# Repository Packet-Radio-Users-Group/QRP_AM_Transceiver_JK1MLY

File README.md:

ブロックダイアグラムが学べる　QRPトランシーバ基板

無線機の基本的な動作を知るため、振幅変調（amplitude modulation）を使った簡易的な無線機を作り、回路の定数やデバイスを変えたり、動作波形を見たりするする基板について扱う

以下の構成でファイルは保存する

assembly  提供する基板に部品を実装する手引き　pdf版の回路図、excel版の部品表を含む

caddata   KiCadのデータ

document  使っている部品、基板などに関する情報

guidance  どのように実験をしていくかの手引き

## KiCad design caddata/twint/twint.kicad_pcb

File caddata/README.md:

KICadデータ

am-pcb1
　思い立って最初に作ったもの
（この基板で実験して、28M・10mWの免許を取得）

am-pcb2
　pcb1を作り直そうとしたもの
（リファイン前提で先に番号を取ったが色々と変えることにしてボツ）

am-pcb3
　受信のミキサをICにしたもの
（動作を学ぶためにはトランジスタの考えに戻ってボツ）

am-pcb4
　実験用として使うための改良
（ハムフェア2024で頒布）

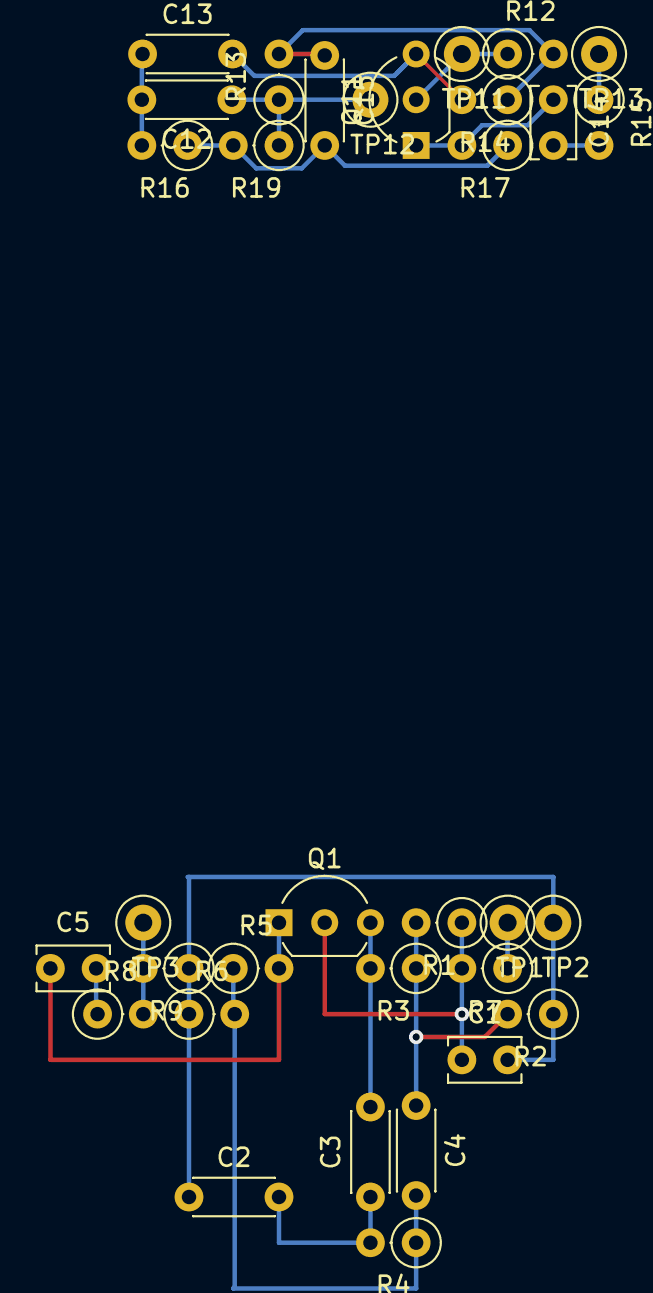
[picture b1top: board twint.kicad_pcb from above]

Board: 2 copper layers, 33 parts (0 on the bottom side), 18 nets.

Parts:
C1, C5, C14: 0.1u; C_Disc_P2.54mm
C2, C3, C12, C13: 0.01u; C_Disc_P5.12mm
C4, C15: 0.033u; C_Disc_P5.12mm
Q1, Q11: 2SC1815; TO-92_Inline_Wide
R1, R12: 22k; R_Axial_DIN0207_L6.3mm_D2.5mm_P2.54mm_Vertical
R2, R13: 33k; R_Axial_DIN0207_L6.3mm_D2.5mm_P2.54mm_Vertical
R3: 10k; R_Axial_DIN0207_L6.3mm_D2.5mm_P2.54mm_Vertical
R4, R16: 4.7k; R_Axial_DIN0207_L6.3mm_D2.5mm_P2.54mm_Vertical
R5, R7, R17: 100; R_Axial_DIN0207_L6.3mm_D2.5mm_P2.54mm_Vertical
R6, R19: 3.3k; R_Axial_DIN0207_L6.3mm_D2.5mm_P2.54mm_Vertical
R8, R15: 100k; R_Axial_DIN0207_L6.3mm_D2.5mm_P2.54mm_Vertical
R9: 1k; R_Axial_DIN0207_L6.3mm_D2.5mm_P2.54mm_Vertical
R14: 15k; R_Axial_DIN0207_L6.3mm_D2.5mm_P2.54mm_Vertical
TP1, TP11: VCC; TestPoint_Loop_D2.50mm_Drill1.0mm
TP2, TP12: GND; TestPoint_Loop_D2.50mm_Drill1.0mm
TP3, TP13: OUT; TestPoint_Loop_D2.50mm_Drill1.0mm

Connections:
GND: C1.2, C2.1, C12.1, R2.1, R6.1, R9.1, R13.1, R19.1, TP2.1, TP12.1
unnamed: C2.2, C3.1, R4.2
unnamed: C4.1, R1.2, R2.2, R3.1
unnamed: C4.2, R4.1, R5.1, R6.2
unnamed: C5.2, R8.1
unnamed: C12.2, C13.1, R16.2
unnamed: C14.2, R15.2
unnamed: C15.1, R12.2, R13.2, R14.1
unnamed: C15.2, R16.1, R17.1, R19.2
unnamed: C3.2, Q1.3 (B), R3.2
unnamed: C1.1, Q1.2 (C), R1.1, R7.2
unnamed: C5.1, Q1.1 (E), R5.2
unnamed: C13.2, Q11.3 (B), R14.2
unnamed: Q11.2 (C), R12.1
unnamed: C14.1, Q11.1 (E), R17.2
unnamed: R7.1, TP1.1
unnamed: R8.2, R9.2, TP3.1
unnamed: R15.1, TP13.1

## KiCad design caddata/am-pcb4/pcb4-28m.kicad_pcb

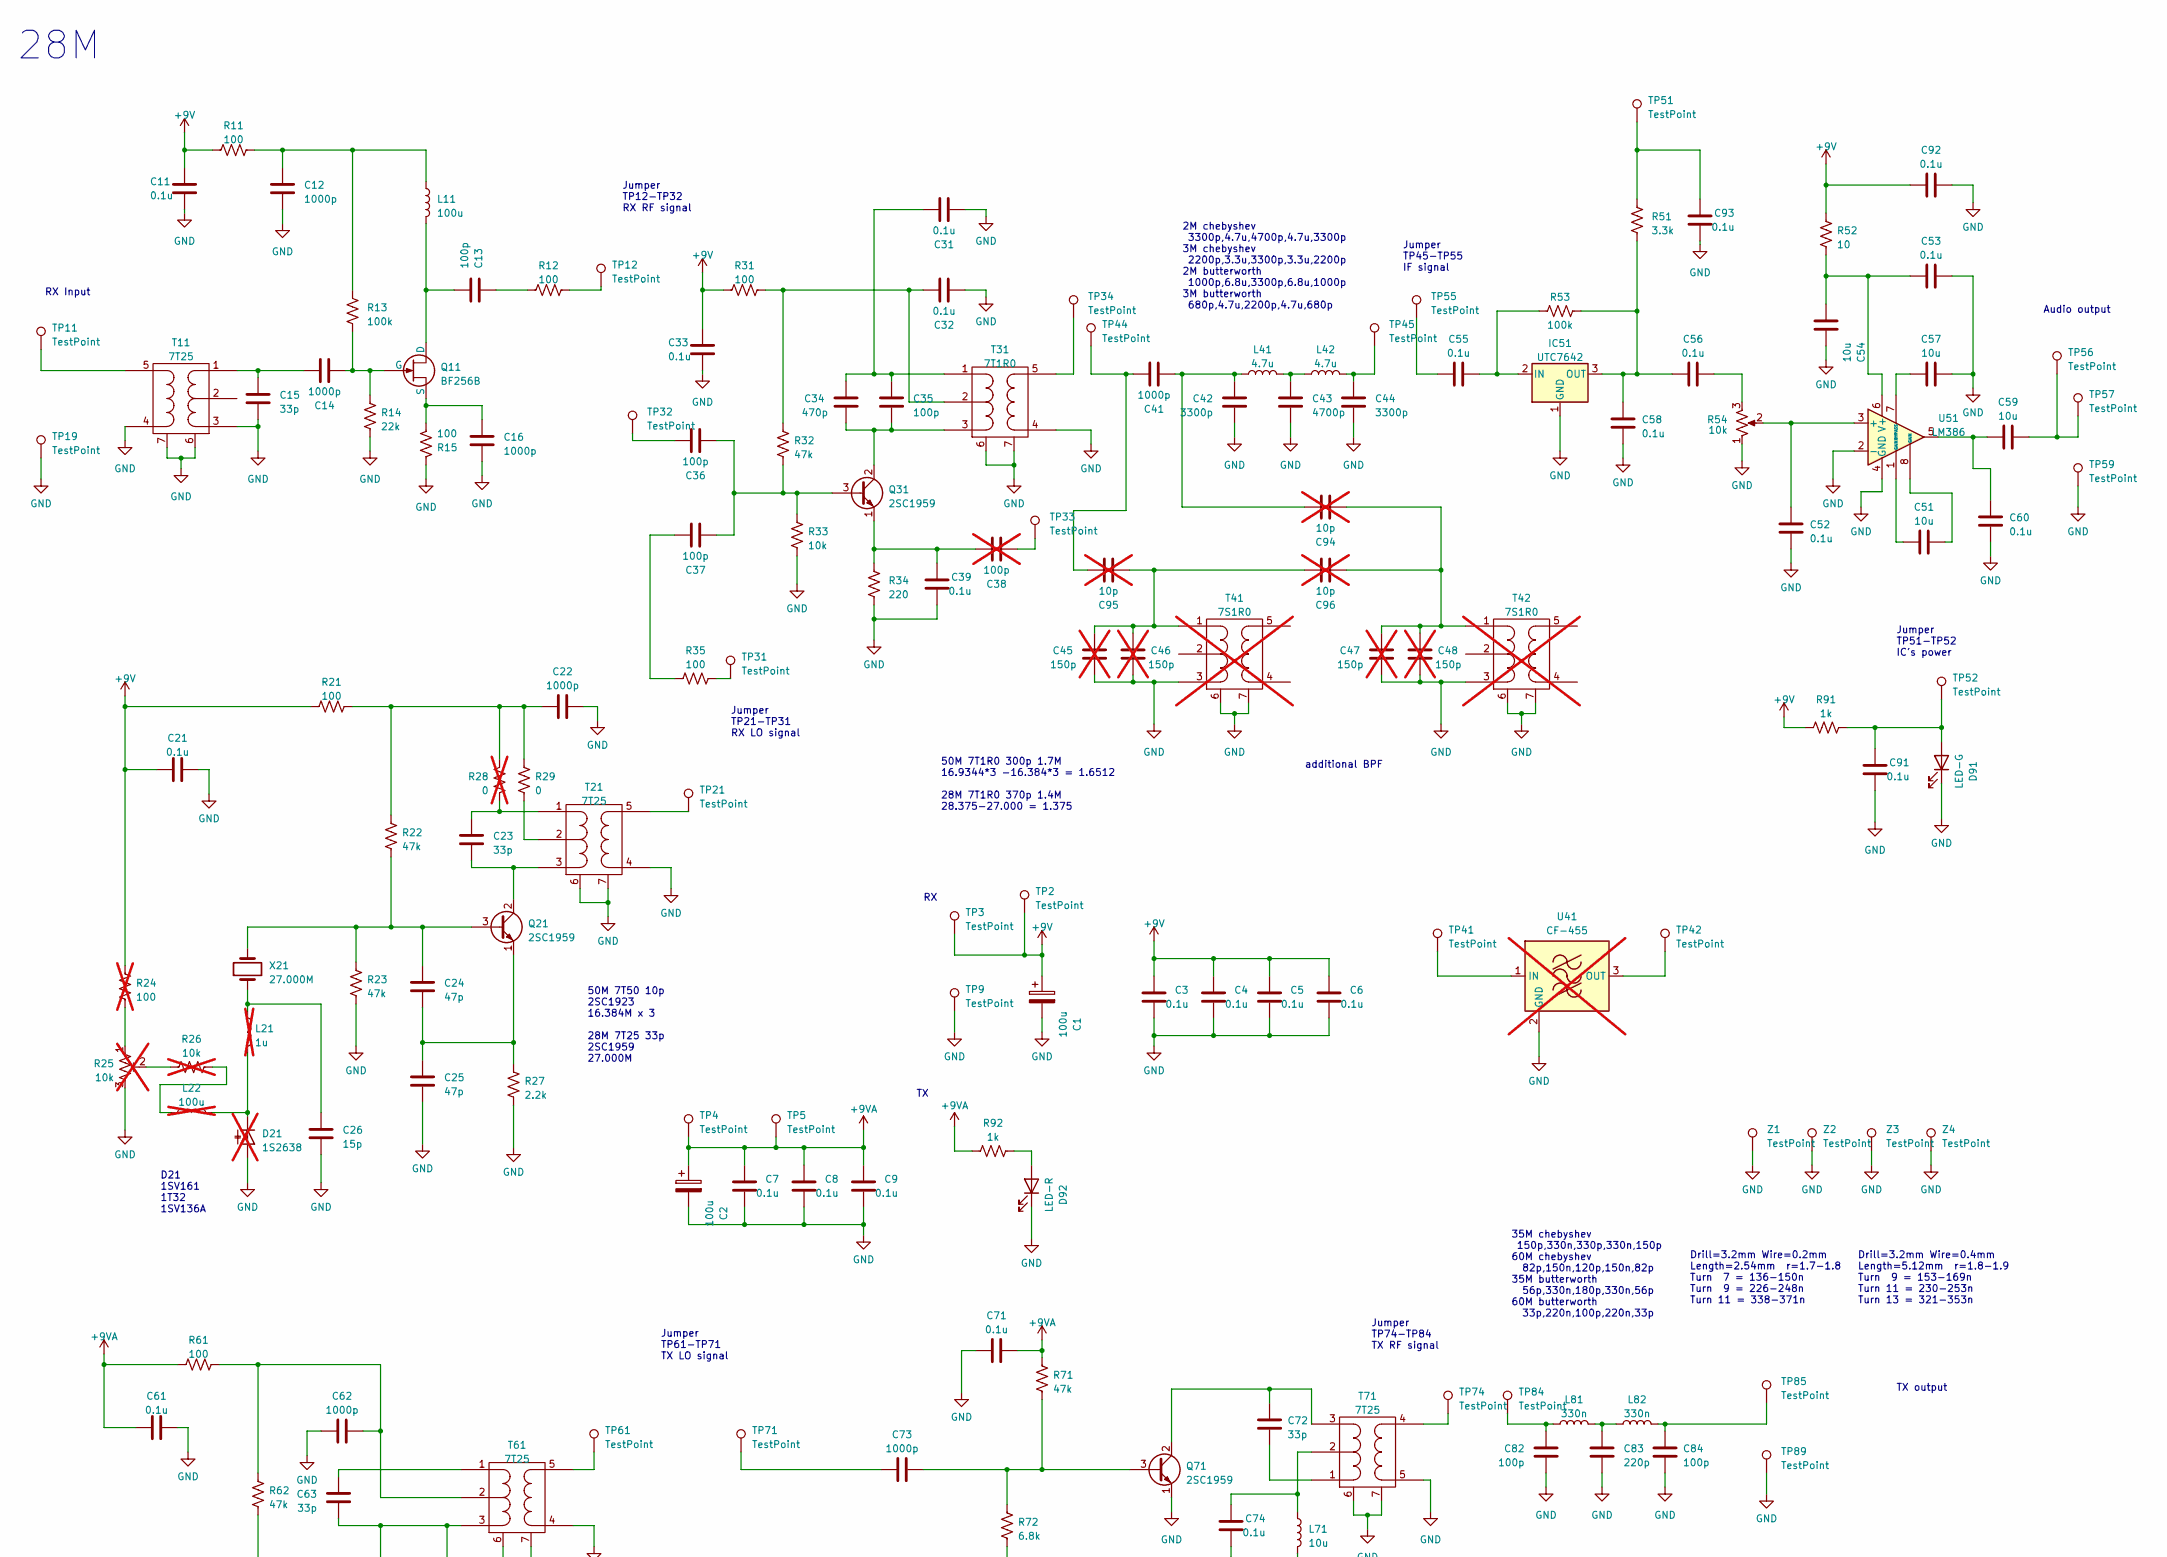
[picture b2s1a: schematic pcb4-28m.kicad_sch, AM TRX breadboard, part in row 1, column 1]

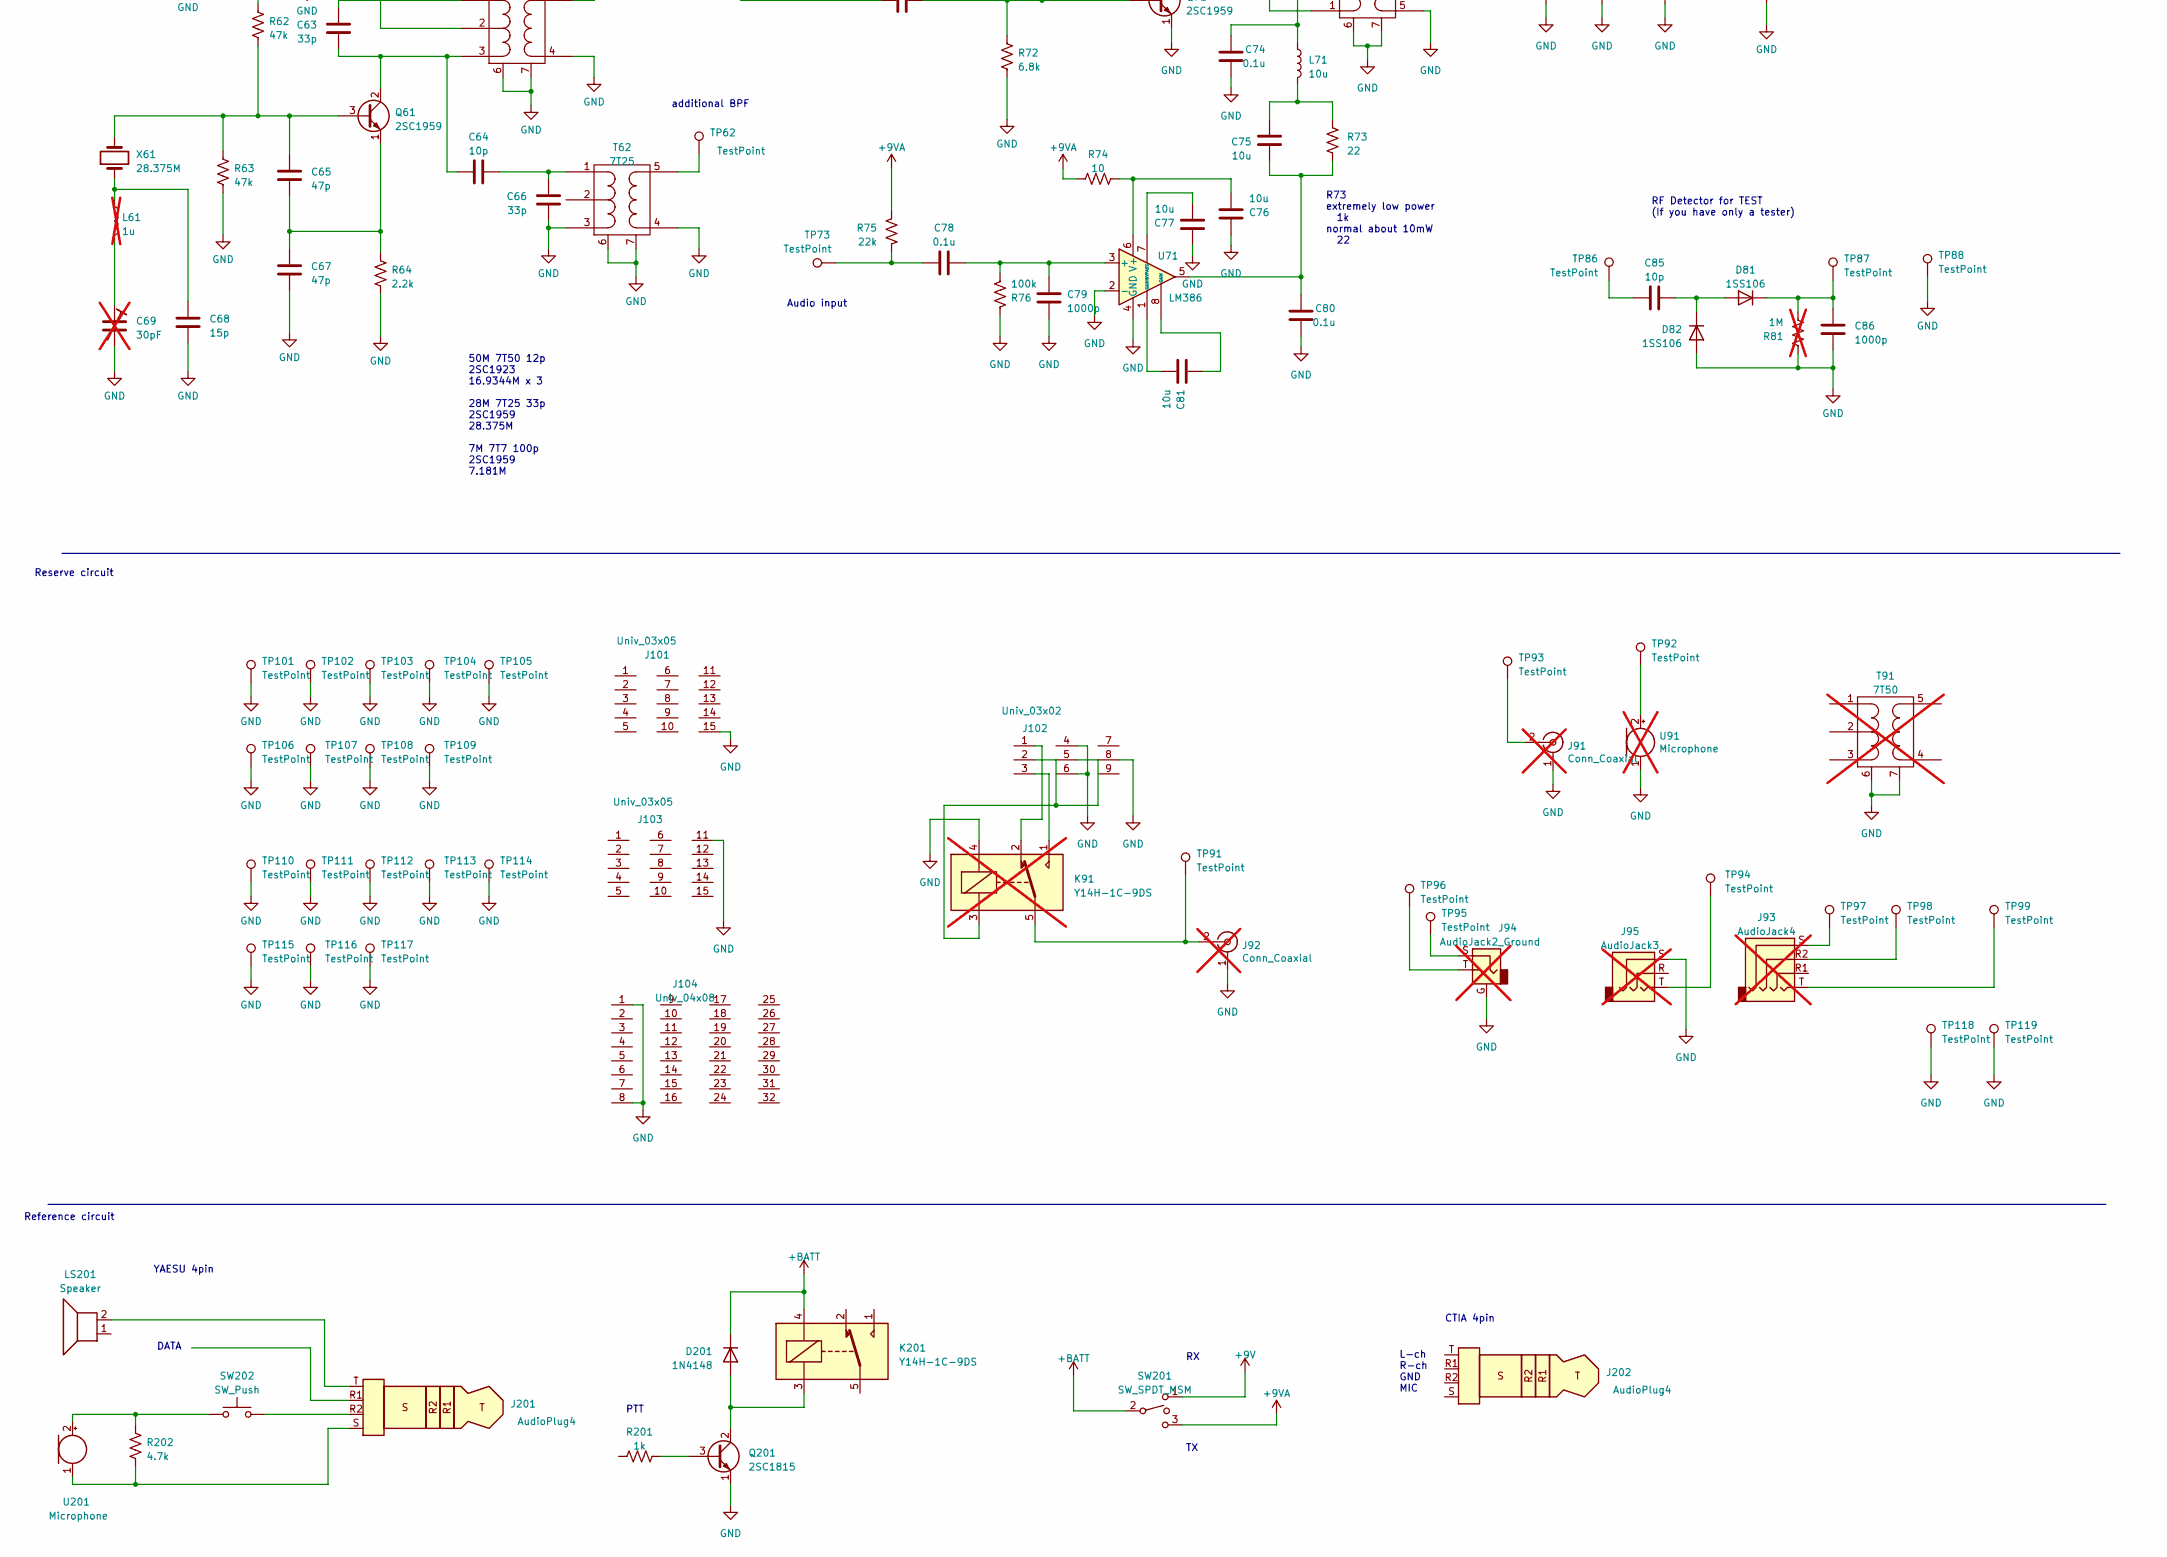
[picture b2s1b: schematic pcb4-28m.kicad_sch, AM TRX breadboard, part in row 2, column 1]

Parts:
C1, C2: 100u; CP_Radial_D7.5mm_P2.54mm_dot
C3, C4, C5, C6, C7, C8, C9, C11, C21, C31, C32, C33, C39, C52, C53, C55, C56, C58, C60, C61, C71, C74, C78, C80, C91, C92, C93: 0.1u; C_Disc_P2.54mm
C12, C14, C16, C22, C41, C62, C73, C79, C86: 1000p; C_Disc_P2.54mm
C13, C35, C36, C37, C82, C84: 100p; C_Disc_P2.54mm
C15, C23, C63, C66, C72: 33p; C_Disc_P2.54mm
C24, C25, C65, C67: 47p; C_Disc_P2.54mm
C26, C68: 15p; C_Disc_P2.54mm
C34: 470p; C_Disc_P2.54mm
C38: 100p; C_Disc_P2.54mm; not fitted
C42, C44: 3300p; C_Disc_P2.54mm
C43: 4700p; C_Disc_P2.54mm
C45, C46, C47, C48: 150p; C_Disc_P2.54mm; not fitted
C51, C54, C57, C59, C75, C76, C77, C81: 10u; C_Disc_P5.12mm
C64, C85: 10p; C_Disc_P2.54mm
C69: 30pF; C_TRIM_P6.00mm; not fitted
C83: 220p; C_Disc_P2.54mm
C94, C95, C96: 10p; C_Disc_P2.54mm; not fitted
D21: 1S2638; D_T-1_P5.08mm_Horizontal; not fitted
D81, D82: 1SS106; D_A-405_P2.54mm_Vertical_AnodeUp
D91: LED-G; LED_D3.0mm
D92: LED-R; LED_D3.0mm
D201: 1N4148; D_A-405_P2.54mm_Vertical_AnodeUp
IC51: UTC7642; TO-92_Inline_Wide
J91, J92: Conn_Coaxial; RF_SMA_Vertical_5-1814832-1; not fitted
J93: AudioJack4; Jack_3.5mm_GB-35J-4CW-BM; not fitted
J94: AudioJack2_Ground; Jack_3.5mm_CUI_SJ1-3525N_Horizontal; not fitted
J95: AudioJack3; Jack_3.5mm_GB-35J-3CWS-BM; not fitted
J101, J103: Univ_03x05; univ_03x05
J102: Univ_03x02; univ_03x03
J104: Univ_04x08; univ_04x08
J201, J202: AudioPlug4
K91: Y14H-1C-9DS; Relay_SPDT_HsinDa_Y14; not fitted
K201: Y14H-1C-9DS; Relay_SPDT_HsinDa_Y14
L11: 100u; R_Axial_DIN0207_L6.3mm_D2.2mm_P2.54mm_Vertical
L21, L61: 1u; R_Axial_DIN0207_L6.3mm_D2.2mm_P2.54mm_Vertical; not fitted
L22: 100u; R_Axial_DIN0207_L6.3mm_D2.2mm_P2.54mm_Vertical; not fitted
L41, L42: 4.7u; R_Axial_DIN0207_L6.3mm_D2.2mm_P2.54mm_Vertical
L71: 10u; R_Axial_DIN0207_L6.3mm_D2.2mm_P2.54mm_Vertical
L81, L82: 330n; R_Axial_DIN0207_L6.3mm_D2.2mm_P2.54mm_Vertical
LS201: Speaker
Q11: BF256B; TO-92_Inline_Wide
Q21, Q31, Q61, Q71: 2SC1959; TO-92_Inline_Wide
Q201: 2SC1815; TO-92_Inline_Wide
R11, R12, R15, R21, R31, R35, R61: 100; R_Axial_DIN0207_L6.3mm_D2.2mm_P2.54mm_Vertical
R13, R53, R76: 100k; R_Axial_DIN0207_L6.3mm_D2.2mm_P2.54mm_Vertical
R14, R75: 22k; R_Axial_DIN0207_L6.3mm_D2.2mm_P2.54mm_Vertical
R22, R23, R32, R62, R63, R71: 47k; R_Axial_DIN0207_L6.3mm_D2.2mm_P2.54mm_Vertical
R24: 100; R_Axial_DIN0207_L6.3mm_D2.2mm_P2.54mm_Vertical; not fitted
R25: 10k; Potentiometer_1; not fitted
R26: 10k; R_Axial_DIN0207_L6.3mm_D2.2mm_P2.54mm_Vertical; not fitted
R27, R64: 2.2k; R_Axial_DIN0207_L6.3mm_D2.2mm_P2.54mm_Vertical
R28: 0; R_Axial_DIN0207_L6.3mm_D2.2mm_P2.54mm_Vertical; not fitted
R29: 0; R_Axial_DIN0207_L6.3mm_D2.2mm_P2.54mm_Vertical
R33: 10k; R_Axial_DIN0207_L6.3mm_D2.2mm_P2.54mm_Vertical
R34: 220; R_Axial_DIN0207_L6.3mm_D2.2mm_P2.54mm_Vertical
R51: 3.3k; R_Axial_DIN0207_L6.3mm_D2.2mm_P2.54mm_Vertical
R52, R74: 10; R_Axial_DIN0207_L6.3mm_D2.2mm_P2.54mm_Vertical
R54: 10k; Potentiometer_1
R72: 6.8k; R_Axial_DIN0207_L6.3mm_D2.2mm_P2.54mm_Vertical
R73: 22; R_Axial_DIN0207_L6.3mm_D2.2mm_P2.54mm_Vertical
R81: 1M; R_Axial_DIN0207_L6.3mm_D2.2mm_P2.54mm_Vertical; not fitted
R91, R92, R201: 1k; R_Axial_DIN0207_L6.3mm_D2.2mm_P2.54mm_Vertical
R202: 4.7k; R_Axial_DIN0207_L6.3mm_D2.2mm_P2.54mm_Vertical
SW201: SW_SPDT_MSM
SW202: SW_Push
T11, T21, T61, T62, T71: 7T25; coil_7mm
T31: 7T1R0; coil_7mm
T41, T42: 7S1R0; coil_7mm; not fitted
T91: 7T50; coil_7mm; not fitted
TP2, TP5, TP56, TP91, TP92, TP93, TP94, TP95, TP96, TP97, TP98, TP99, TP118, TP119: TestPoint; TestPoint_pad_only_Drill1.0mm
TP3, TP4, TP9, TP11, TP12, TP19, TP21, TP31, TP32, TP33, TP34, TP41, TP42, TP44, TP45, TP51, TP52, TP55, TP57, TP59, TP61, TP62, TP71, TP73, TP74, TP84, TP85, TP86, TP89, TP101, TP102, TP103, TP104, TP105, TP106, TP107, TP108, TP109, TP110, TP111, TP112, TP113, TP114, TP115, TP116, TP117: TestPoint; TestPoint_Loop_D2.50mm_Drill1.0mm
TP87, TP88: TestPoint; TestPoint_Loop_D3.80mm_Drill2.5mm
U41: CF-455; CF-3P; not fitted
U51, U71: LM386; DIP-8_W7.62mm_Socket
U91: Microphone; Mic_CMA-4544PF-W; not fitted
U201: Microphone
X21: 27.000M; Crystal_HC49-U_Vertical
X61: 28.375M; Crystal_HC49-U_Vertical
Z1, Z2, Z3, Z4: TestPoint; TestPoint_Drill3mm

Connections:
+9V: C1.1, C3.1, C4.1, C5.1, C6.1, C11.1, C21.1, C33.1, C92.1, R11.1, R21.1, R24.1, R31.1, R52.1, R91.1, TP2.1, TP3.1
+9VA: C2.1, C7.1, C8.1, C9.1, C61.1, C71.2, R61.1, R71.1, R74.1, R75.1, R92.1, TP4.1, TP5.1
GND: C1.2, C2.2, C3.2, C4.2, C5.2, C6.2, C7.2, C8.2, C9.2, C11.2, C12.2, C15.2, C16.2, C21.2, C22.1, C25.2, C26.2, C31.2, C32.2, C33.2, C39.2, C42.2, C43.2, C44.2, C45.2, C46.2, C47.2, C48.2, C52.1, C53.2, C54.2, C57.2, C58.1, C60.1, C61.2, C62.1, C66.2, C67.2, C68.2, C69.2, C71.1, C74.2, C76.2, C77.2, C79.2, C80.2, C82.2, C83.2, C84.2, C86.2, C91.2, C92.2, C93.2, D21.2 (A), D82.2 (A), D91.1 (K), D92.1 (K), IC51.1 (GND), J91.1 (G), J92.1 (G), J94.G, J95.S, J101.15, J102.4, J102.6, J102.8, J103.11, J104.1, J104.8, K91.4, Q71.1 (E), R14.2, R15.1, R23.1, R25.3, R27.1, R33.1, R34.1, R54.1, R63.1, R64.1, R72.1, R76.1, R81.1, T11.3 (PR2), T11.4 (S1), T11.6 (G1), T11.7 (G2), T21.4 (S1), T21.6 (G1), T21.7 (G2), T31.4 (S1), T31.6 (G1), T31.7 (G2), T41.3 (PR2), T41.6 (G1), T41.7 (G2), T42.3 (PR2), T42.6 (G1), T42.7 (G2), T61.4 (S1), T61.6 (G1), T61.7 (G2), T62.3 (PR2), T62.4 (S1), T62.6 (G1), T62.7 (G2), T71.5 (S1), T71.6 (G1), T71.7 (G2), T91.6 (G1), T91.7 (G2), TP9.1, TP19.1, TP59.1, TP88.1, TP89.1, TP101.1, TP102.1, TP103.1, TP104.1, TP105.1, TP106.1, TP107.1, TP108.1, TP109.1, TP110.1, TP111.1, TP112.1, TP113.1, TP114.1, TP115.1, TP116.1, TP117.1, TP118.1, TP119.1, U41.2 (GND), U51.2 (-), U51.4 (GND), U71.2 (-), U71.4 (GND), U91.1 (-), Z1.1, Z2.1, Z3.1, Z4.1
unnamed: C12.1, L11.1, R11.2, R13.1
unnamed: C13.1, R12.1
unnamed: C22.2, R21.2, R22.1, R28.1, R29.1
unnamed: C26.1, L21.1, X21.1
unnamed: C36.1, TP32.1
unnamed: C37.1, R35.1
unnamed: C38.2, TP33.1
unnamed: C41.1, C95.1, TP44.1
unnamed: C41.2, C42.1, C94.1, L41.1
unnamed: C43.1, L41.2, L42.1
unnamed: C44.1, L42.2, TP45.1
unnamed: C51.1, U51.1 (GAIN)
unnamed: C51.2, U51.8 (GAIN)
unnamed: C55.1, TP55.1
unnamed: C56.2, R54.3
unnamed: C59.1, C60.2, U51.5
unnamed: C59.2, TP56.1, TP57.1
unnamed: C68.1, L61.1, X61.1
unnamed: C69.1, L61.2
unnamed: C73.1, TP71.1
unnamed: C75.1, C80.1, R73.2, U71.5
unnamed: C75.2, L71.2, R73.1
unnamed: C78.1, R75.2, TP73.1
unnamed: C81.1, U71.1 (GAIN)
unnamed: C81.2, U71.8 (GAIN)
unnamed: C82.1, L81.1, TP84.1
unnamed: C83.1, L81.2, L82.1
unnamed: C84.1, L82.2, TP85.1
unnamed: C85.1, TP86.1
unnamed: C93.1, R51.1, TP51.1
unnamed: D21.1 (K), L21.2, L22.2
unnamed: C85.2, D81.2 (A), D82.1 (K)
unnamed: C86.1, D81.1 (K), R81.2, TP87.1
unnamed: C91.1, D91.2 (A), R91.2, TP52.1
unnamed: D92.2 (A), R92.2
unnamed: D201.1 (K), K201.4, SW201.2
unnamed: D201.2 (A), K201.3, Q201.2 (C)
unnamed: C55.2, IC51.2 (IN), R53.2
unnamed: C56.1, C58.2, IC51.3 (OUT), R51.2, R53.1
unnamed: J91.2 (S), TP93.1
unnamed: J92.2 (S), K91.5, K91.6, TP91.1
unnamed: J93.R2, TP98.1
unnamed: J93.S, TP97.1
unnamed: J93.T, TP99.1
unnamed: J94.S, TP95.1
unnamed: J94.T, TP96.1
unnamed: J95.T, TP94.1
unnamed: J102.1, K91.2
unnamed: J102.2, J102.5, K91.3
unnamed: J102.3, K91.1
unnamed: J201.R2, SW202.2
unnamed: J201.T, LS201.2
unnamed: K201.5, K201.6
unnamed: L22.1, R26.2
unnamed: C13.2, L11.2, Q11.3 (D)
unnamed: C14.2, Q11.1 (G), R13.2, R14.1
unnamed: C16.1, Q11.2 (S), R15.2
unnamed: C24.1, Q21.3 (B), R22.2, R23.2, X21.2
unnamed: C23.2, Q21.2 (C), T21.3 (PR2)
unnamed: C24.2, C25.1, Q21.1 (E), R27.2
unnamed: C36.2, C37.2, Q31.3 (B), R32.2, R33.2
unnamed: C34.2, C35.2, Q31.2 (C), T31.3 (PR2)
unnamed: C38.1, C39.1, Q31.1 (E), R34.2
unnamed: C65.1, Q61.3 (B), R62.2, R63.2, X61.2
unnamed: C63.2, C64.1, Q61.2 (C), T61.3 (PR2)
unnamed: C65.2, C67.1, Q61.1 (E), R64.2
unnamed: C73.2, Q71.3 (B), R71.2, R72.2
unnamed: C72.1, Q71.2 (C), T71.3 (PR1)
unnamed: R12.2, TP12.1
unnamed: R24.2, R25.1
unnamed: R25.2, R26.1
unnamed: R35.2, TP31.1
unnamed: C14.1, C15.1, T11.1 (PR1)
unnamed: T11.5 (S2), TP11.1
unnamed: R29.2, T21.2 (PM)
unnamed: C23.1, R28.2, T21.1 (PR1)
unnamed: T21.5 (S2), TP21.1
unnamed: C32.1, R31.2, R32.1, T31.2 (PM)
unnamed: C31.1, C34.1, C35.1, T31.1 (PR1)
unnamed: T31.5 (S2), TP34.1
unnamed: C45.1, C46.1, C95.2, C96.1, T41.1 (PR1)
unnamed: C47.1, C48.1, C94.2, C96.2, T42.1 (PR1)
unnamed: C62.2, R61.2, R62.1, T61.2 (PM)
unnamed: C63.1, T61.1 (PR1)
unnamed: T61.5 (S2), TP61.1
unnamed: C64.2, C66.1, T62.1 (PR1)
unnamed: T62.5 (S2), TP62.1
unnamed: C74.1, L71.1, T71.2 (PM)
unnamed: C72.2, T71.1 (PR2)
unnamed: T71.4 (S2), TP74.1
unnamed: TP41.1, U41.1 (IN)
unnamed: TP42.1, U41.3 (OUT)
unnamed: C52.2, R54.2, U51.3 (+)
unnamed: C57.1, U51.7 (BYPASS)
unnamed: C53.1, C54.1, R52.2, U51.6 (V+)
unnamed: C78.2, C79.1, R76.2, U71.3 (+)
unnamed: C77.1, U71.7 (BYPASS)
unnamed: C76.1, R74.2, U71.6 (V+)
unnamed: TP92.1, U91.2 (+)

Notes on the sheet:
Reference circuit
additional BPF
Jumper TP61-TP71 TX LO signal
L-ch R-ch GND MIC
28M
Reserve circuit
50M 7T1R0 300p 1.7M 16.9344*3 -16.384*3 = 1.6512 28M 7T1R0 370p 1.4M 28.375-27.000 = 1.375
D21 1SV161 1T32 1SV136A
CTIA 4pin
Audio output
Jumper TP74-TP84 TX RF signal
DATA
RX Input
R73 extremely low power 1k normal about 10mW 22
Jumper TP45-TP55 IF signal
Audio input
Drill=3.2mm Wire=0.4mm Length=5.12mm r=1.8-1.9 Turn 9 = 153-169n Turn 11 = 230-253n Turn 13 = 321-353n
2M chebyshev 3300p,4.7u,4700p,4.7u,3300p 3M chebyshev 2200p,3.3u,3300p,3.3u,2200p 2M butterworth 1000p,6.8u,3300p,6.8u,1000p 3M butterworth 680p,4.7u,2200p,4.7u,680p
Jumper TP12-TP32 RX RF signal
Jumper TP21-TP31 RX LO signal
Drill=3.2mm Wire=0.2mm Length=2.54mm r=1.7-1.8 Turn 7 = 136-150n Turn 9 = 226-248n Turn 11 = 338-371n
PTT
TX output
YAESU 4pin
50M 7T50 12p 2SC1923 16.9344M x 3 28M 7T25 33p 2SC1959 28.375M 7M 7T7 100p 2SC1959 7.181M
RF Detector for TEST (If you have only a tester)
35M chebyshev 150p,330n,330p,330n,150p 60M chebyshev 82p,150n,120p,150n,82p 35M butterworth 56p,330n,180p,330n,56p 60M butterworth 33p,220n,100p,220n,33p
50M 7T50 10p 2SC1923 16.384M x 3 28M 7T25 33p 2SC1959 27.000M
Jumper TP51-TP52 IC's power

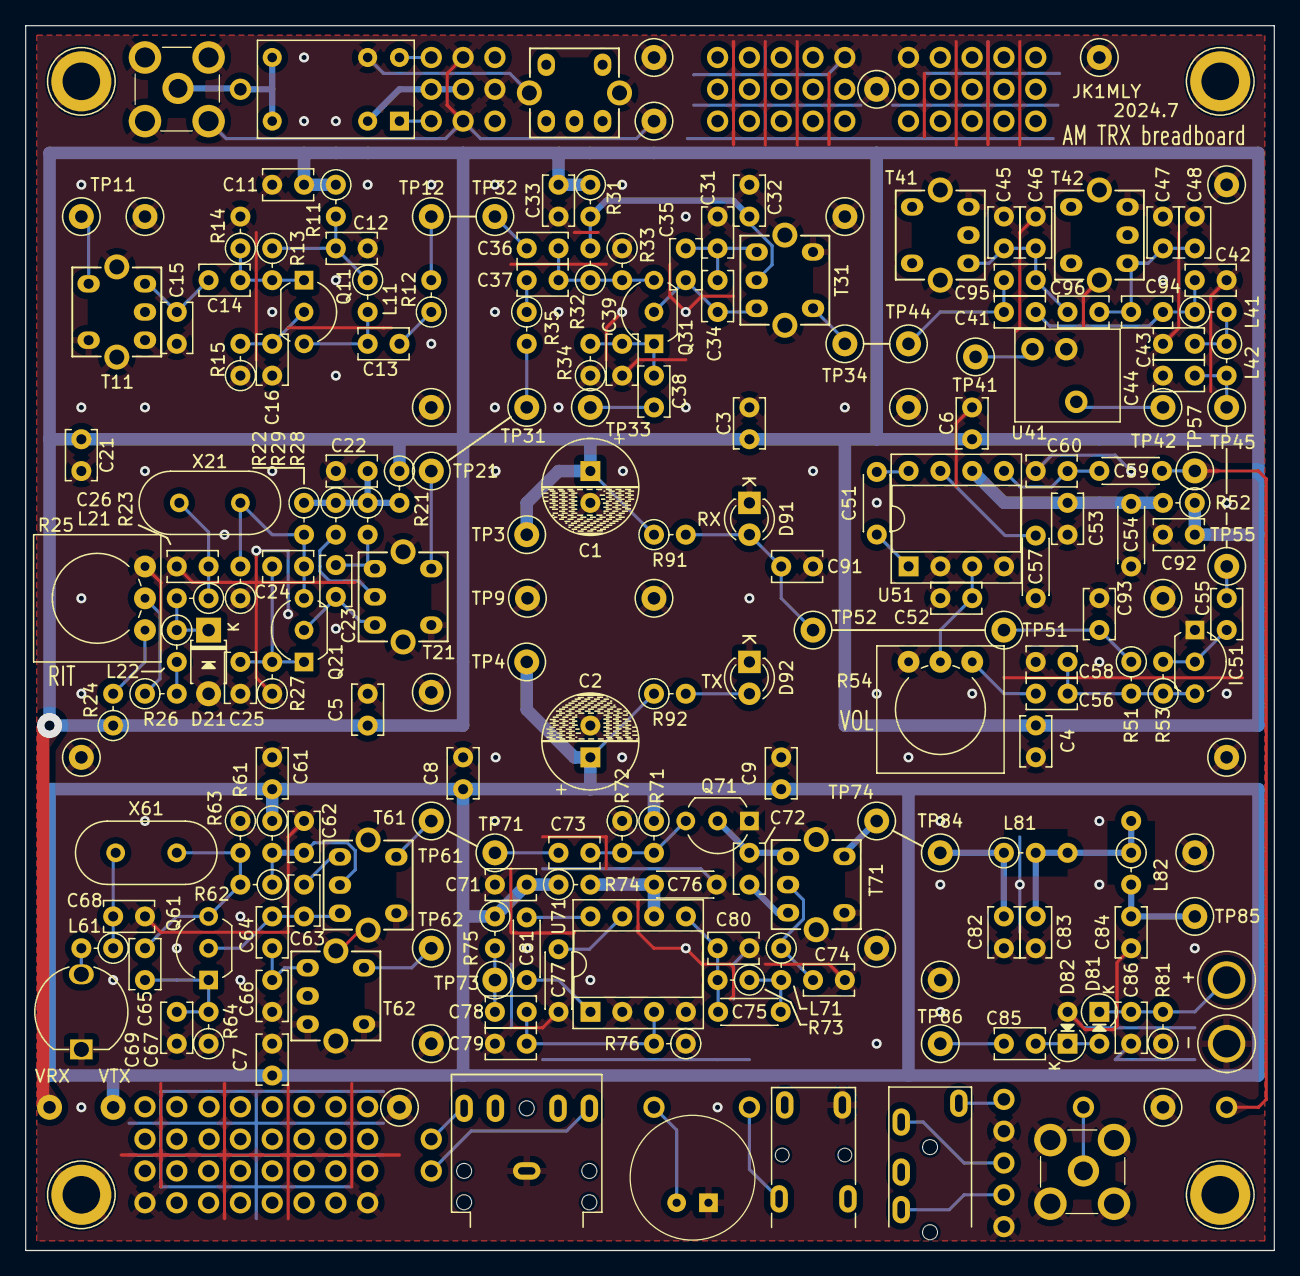
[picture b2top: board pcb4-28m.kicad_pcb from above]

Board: 2 copper layers, 99.7 x 97.8 mm, 226 parts (0 on the bottom side), 97 nets.
